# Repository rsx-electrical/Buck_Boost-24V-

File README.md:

# Buck_Boost
Designed to provide a regulated 24V output from a 6S (24V nominal) battery pack with an input range of about 19–25V.
Intended for use in a rover system powering comms hardware (TpLink POE; JETSON AGX ORIN).

# Workflow
1. Message Discord that you are working in the repo. Nobody else can work on it once you message.
2. `git clone git@github.com:rsx-electrical/Buck_Boost-24V-.git`
3. Edit 4_switch_Buck_Boost
4. Edit the README in 4_switch_Buck_Boost to describe what your commit does and why the changes were made.
5. Save a zip file version of your finished work into History Folder. 
- File should named `<date/time>_<name>_<brief_description_of_changes>`
5. Stage the files you want to commit. See "How to commit changes" bellow. 
6. `git commit -m <commit message>`
7. `git push`
8. Yay:). You are done

# Specs 
Vin: 19–25V (6S Li-ion pack)
Vout: 24V nominal
Estimated power: 100W total (More than sum of both loads, some margin for overhead and future changes)

# Notes
Design is still in development; input range, component choices, and power ratings may change. Focus is on stable 24V output, good efficiency, and reliable operation in a mobile rover environment.Future updates will include board revisions, layout improvements, and performance testing.

# How to commit changes
A file with changes can be in one of three states: untracked, modified, or staged. Only staged files are included in the next commit. 
- `git status`: command to see the status of the files you have modified
## Staged files
Staged changes are changes in files that have been marked in git to be included in the next commit. The section labeled "Changes to be committed" in git status shows these staged files.
If you stage a file and then make additional changes to it, those new changes are not staged and will not be included in the next commit. To include them, you need to stage the file again.
- `git add <file_name> `: command to stage a file
- `git add . `: stage all files with changes in them. Be careful as this will also stage untracked files which often we do not want to be staged. 
- `git restore --staged <file>` : command to unstage a file
## Tracked Files
Tracked files are files that git is already monitoring for changes, meaning they were previously committed and git keeps track of any modifications to them. 
## Untracked files
Untracked files are files in your working directory that Git does not yet know about. These are sometimes autogenerated files or files for certain settings in your local repo. An example on a Mac is .DS_Store. This .DS_Store file s a hidden file created by macOS in folders to store custom metadata about that folder, like icon positions, view settings, and window size. This is not a file that we want pushed to the remote repository.

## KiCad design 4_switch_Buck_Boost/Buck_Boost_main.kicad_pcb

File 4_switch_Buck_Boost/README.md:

# Purpose of readme

This README describes each commit made to the `4_switch_Buck_Boost folder`. Add the most recent changes at the top, but below this "Purpose of readme" section.
Each commit section title in this README should follow this format: `Date, Name, Title of Commit`

## 11-07 William -- GND plane extension, board outline, connectivity fixes

Layout:

- Extended the F.Cu GND plane through the centre (including under L1) and filled the top centre with GND.
- GNDA is now an island on In1, tied to GND through NT1 netlist at the U102 exposed pad.
- Rerouted LSP/LSN as a matched pair, added the Vout pour, fixed tight clearances (FB, Vin near Q102 gate).
- Moved TP6 to R104. Made F1/F2, TP1/TP11 and the BAT/OUTPUT pours symmetrical.
- 45° corner cuts on all pours. Board outline added: 110 x 90 mm,

Fixed opens that were already in the layout:

- SW1/SW2: U102 pins 3/26 and C8/C9 were not connected to the switch nodes. Now routed via TP3/TP4.
- In2 Vin plane was not connected to the rest of Vin. Added around 30 stitching vias (14 around the Q104 drain for heat).
- ENABLE (J3/TP10 to C114), R1 to D1, C7 GND via, U101 GND pins, FB gaps.
- R7 Kelvin footprint: added net-tie pad groups (1,2)(3,4) so DRC does not flag shorts.

Fab: 2 oz outer (for higher current) and 1 oz inner copper

## 10-18 William -- Reconfigured Analog traces and GNDA island

Configured all the analog traces and GNDA island for the new LT8390 footprint

## 10-02 William -- SW1, GND, Vout, pores

Draw and filled all the pores above along with the vias.

## 09-22 Maria -- Rsense footprint

Added Littelfuse L4CL2512 footprint for the sensing resistors. Reangered power path to accommodate size change in new resistor and inductor footprints.

## 09-20, William -- 4 Layers GND and GNDA plane

Made all the 4 Layers, Top-GND&GNDA-Vin-GND. Connected both GND and GNDA together thorugh a via and shorted resistor to prevent DRC error. Has connected all the vias in analog stage.

## 09-19, William -- Update footprint, Analog traces

Updated FETs symbols footprints, Inductor footprints, Connect traces for analog stage

## 09-12, Maria -- Reverse Polarity Protection

Added reverse polarity protection to the schematic and layout. Placed between the fuse and vin.

## 07-17, Anthony -- Template Starting Changes

Went ahead and hunkered down on some more final changes to the analog component placement, providing a tighter, more optimized orientation for building traces, closer/more compact. Def mess around with them if need be, esp the gate driver series resistors, those can go wherever you want, just pls keep the BOOTstrap caps as close as possible. With placement of analog passive components, gonna like draw gate signal traces as copper pours, up to discretion of later design review. Additionally, settled on shunt footprint/placement without compromising hot loop layout (best we gonna do, had to sacrifice snub filter, but this is optional, pick them up later). And, upgraded inductor footprint to be more 'on-brand' with the power inductors you're likely gonna find for the necessary L (uH) values that 55V/0.55A, 12V/5A are gonna demand. Please feel more than free to change any footprints you see fit. Also, omitted the fan control aux circuit, this is gonna be external to the buck-boost pcb. TLDR: slightly prepared everything to turn this 24V buck-boost into a template PCB for bucking/boosting and buck-boosting for 5V,12V,24V, and 55V.

## 07-03, Maria -- Passive Components, Controller and Auxiliary Circuits

Feedback from the June 3rd commit was that the passive component circuits should be closer to the controller. There is no need to have them so spread out and close to the power path as it should be good to have a trace to the power path. This update moves the feedback circuit, enable circuit and passive components for the controller to be closer to the controller. This update adds traces for these circuits (traces for within these Passive Components and Auxiliary Circuits only) as well as two pores for GNDA and GND (GND pore is the GND for the enable circuit). Please note that I know that the edges of these pores are rough. Turns out I am kinda sucky at drawing out pores. Also not there is no vias added. I am going to assume that these will be added once we agree with the component placement.

## 06-03, Maria -- Passive Components, Controller and Auxiliary Circuits

Added the passive components, controller and auxiliary Circuits to the power path

## 05-23, Maria -- First Attempt at power path

Uhm so this is written on June 3rd because I forgot. Soooooo yeah basically the title, first attempt at full power path.

## 04-03, William -- PCB components placement

Tried to minimize the Hot loops, further optimization may be required

## 03-17, Anthony -- Additional revisions on Schematic for Smooth Layout design for yall

Want to make layout go as smoothly as possible, so just went ahead and ensured all components had appropiate footprints. Also added NTC (temp control) for fan control using heat probe.

## List of stuff

-Added filter caps to Vin and Vout pin connections to LT8390

-Adjusted for larger Cout over Cin to reflect calculated sizing demands.

-Changed Inductor footprint for better saturation current rating/Irms rating, previous one was way to close to our shit, plus this footprint is way more streamlined imo

-Opt to use different footprint for shunt, kicad-preloads are fucking stinky uh uh (DOWNLOAD AND IMPORT SYMBOL AND FOOTPRINT PLEASE: https://www.snapeda.com/parts/KRL3216T4-M-R003-F-T1/Susumu/view-part/ )

-EN/UVLO needs voltage divider network for proper ENABLE, so adjusted level shifter circuit for ~1.2V to be seen at pin EN/UVLO, but still programs for undervoltage lockout when reach ~16V or so, good shutoff conditions in case BMS fucks us somehow -- It's a mandatory feature not preprogrammed like a lot of the TI chips are.

-Better probing points for observing ripple, PWM, or general signals (3 kinds of probe footprints). M3 Mounting holes added as well and dedicated Net tie for GNDA and GND (fuck with footprint if need be)

-Heatsink gonna be adhesive, fuck mounts, also made it an option to use osc freq or triangle spreading +/- 15%. Triangle spread usually better, but can introduce greater voltage ripple so we can place with it using jumper cap and 2x2 head conn setup.

-NTC for temp control fan will prob be wire that sits and probes heatsink, so just a CONN for now, we'll see, up to ya'll.

-All connections on schematic should roughly agree with where they'll go on layout (ie. BST caps near chip and not power stage)

-SMD trimmers, not bulky n shit (THT or SMD, if going near chip, SMD, if away from chip, THT/SMD).

-Snub filter 0805 caps, larger caps capable of handling transient response from fets way better than 402 or 603 so yeye, also shorter fuse holders too.

## 03-14, Anthony -- Final Check on shit

All pin connections/sizing good -- ready for layout

## 03-14, Maria Finish up pins and make it look pretty

I tried to make it look prettier. I may have failed at that but I finished up the pins;).

## 03-07, William, FeedBack loop trimmer and decoupling capacitor addition

Add a trimmer to ensure precise FB voltage of 1V, and a safety margin during tuning. Add Decoupling capacitor for stabilizing voltage.

## 03-06, Maria, LT8390 Pins

To be quite honest the most important part of this commit is probably this readme where I am documenting all of the questions I have about these pins. This commit is mostly my best guess. I hope to get clarification this Saturday ;).

### RT pin

This pin should have a resistor of 75kOhms attached to it. Question is should we have a potentiometer to ensure that we can tune to 75kOhms as all resistors will have some range of error on the resistance value.

### SS pin

All of the example applications have a value of 0.1u F. I don't understand how we determine the minimum soft-start time that we want. We don't add a resistance here because we want to hiccup safety mode, not latch off or keep running mode.

### Vc pin

I am so lost, I don't know my up from down for this pin.

### PGOOD pin

This pin is smth we could connect to an external microcontroller as indicator that the voltage has successfully reached its target. I don't think that this will probably be used. However connect to INTVcc with 100k ohms so that pin is pulled low when the FB pin is within �10 percent of the final regulation voltage. Maybe down the line we will want to connect it to smth, we could leave it hanging if we wanted. A value of 100kohms is used because that is used in all of the example application circuits.

### INTVcc pin

Tie to 4.7uF ceramic capacitor as instructed.

### SYNC/SPREAD

We don't want an external source for the switching. I think we probably want to have the mode with the 15 percent spread around internal oscillator frequency to ensure no sudden noise peaks. Tie this pin to INTVcc.

## 03-05, Maria, Capacitors !!!

Thank you Anthony for the document about filtering ringing and ripple!!! The document helped with this section a lot. Also thank you to the LT890 data sheet for going through a bit about Cin and Cout capacitances.

### Ringing Frequency

Ringing frequency of 75MHz-143MHz. 22nF will filter 30MHZ-100MHz range and 4.7nF will filter 100+MHz range. In a 4-switch buck-boost, the "Active Switching Side" moves depending on the mode (Buck or Boost). Therefore a 22 nF + 4.7 nF stack on required on both the Input and Output power rails to stay protected. At the high frequencies that ringing occurs at, the 15uH inductor between the two switching nodes is 2*pi*freq\*(15e-6). For a frequency of 100MHz this comes to an impedance of 9.5KOhms. Maybe we can consider using snub circuits on the switching nodes? May not be required as power rails are protected.

### Bulk Capacitors

Calculations for the following are seen on this spreadsheet under the Capacitance Values tab: https://docs.google.com/spreadsheets/d/1GE4mJHaV0VTMqPT8AXjkSjW_NcW0vJ0DrAooZ-j17pU/edit?gid=2053012627#gid=2053012627

#### Cout

We want the output ripple to be at most 2 percent of the output voltage which is 0.480V. The output capacitance required to have this output ripple under boost conditions is at least 5.21uF and under buck conditions at least a 0.781uF output capacitance is required. To account for the Boost Right-Half-Plane Zero phenomenon a minimum of 57.9uF output capacitance is required. To account for voltage undershoot an output capacitance of 1.46uF is required. Therefore for the circuit to be functional an output capacitance of at least 57.9uF is required. We want low ESR. Two capacitances of 33uF can be used.

#### Cin

A Cin of at least 1.14uF is required to maintain under a input voltage ripple of 0.512V. However the input capacitance network should support a Irms current of Iout(max)/2 (see pg. 21 of LT8390 data sheet). No capacitor that small can support that large of a current. We also want a very small ESR. Therefore we should have larger capacitance values in parallel to split the current and lower ESR. For electrolytic capacitors that have smaller values their ESR is very large. Is it better to have only ceramic at the beginning. For now, I am going to put a placeholder value of three 22nF electrolytic capacitors or Cin. This will lower ESR and provide required capacitance. Ask this Saturday which type of capacitor would be best here. I feel like it would be ceramic.
####Next Steps
Next steps would be determining the exact capacitors required. Most of this is gonna be a fight of finding capacitors with low ESRs. If all falls apart can just use capacitors with higher values and have more in parallel to lower ESR (generally larger value electrolytic capacitors have lower ESRs). I am uncertain if we are just gonna use capacitors we have in stock. Smth I will have to ask Anthony.

## 02-27, Maria, High Side Switch

2N7002K: rsx nmos
BSS83P: rsx pmos only has Vds of 30V. rsx pmos is cutting it close because our vin can be 25ish. Dangerous if there are any spikes in our Vin. Chosen because it has a Vds of -60V which is very safe.
R106&R105: The Vgs of the pmos (BSS83P) is +/- 20V. Having this voltage divide means that the gate of the pmos will be half the voltage of Vin. This will allow the pmos to turn on when required but have a Vgs range of 9V to 13V when the enable pin is on and it will be around 0 when the enable pin if off. These are aat least 1.46ll safe ranges.

### Next Steps

Find the spec for the LEDs that rsx has in stock. Find out what the input voltage we will get from the microcontroller. Use this information to determine the exact values for the resistors at the gate of the nmos.

### LTSpice Simulation

#### High Side Switch Vin is 25.6V

PMOS high-side switch LTSpice schematic with Vin of 25.6V

When the enable input coming from a microcontroller (enable_vin) is set high, the enable pin (en_pin) on the LT8390 is set high. When the enable input is set low, the enable pin on the LT8390 is set low as well.

The Vgs (Vpmos_gate - Vin) and Vds (Ven_pin - Vin) of the pmos. Vgs is safe within the maximum of +/- 20V. Vds is safe with a maximum of -60V.

The Vgs (Ven_pin) and Vds (Vnmos_drain) of the nmos. Vgs is safe within the maximum of +/- 20V. Vds is safe with a maximum of 60V.

pmos Id is rated for -0.33A, nmos is rated for 320mA. Currents are in a safe range.

#### High Side Switch Vin is 18V

PMOS high-side switch LTSpice schematic with Vin of 18V.

When the enable input coming from a microcontroller (enable_vin) is set high, the enable pin (en_pin) on the LT8390 is set high. When the enable input is set low, the enable pin on the LT8390 is set low as well.

The Vgs (Vpmos_gate - Vin), Vds (Ven_pin - Vin) and Id of the pmos. Vgs is safe within the maximum of +/- 20V. Vds is safe with a maximum of -60V. Id is safe as pmos is rated for -0.33A.

The Vgs (Ven_pin) and Vds (Vnmos_drain) of the nmos. Vgs is safe within the maximum of +/- 20V. Vds is safe with a maximum of 60V.

nmos current is good.

## 02-07, Maria, Reformat to be readable

Reformat to be split up into sections like the example Anthony gave us of a past boost converter. Input filtering capacitors with no values. They are placeholders. Values will need to be determined and number of capacitors will need to be determined.

## 02-05, Maria, connected power path to chip

Yeah I know title doesn't make sense. Added power path (MOSFETTS and inductor) to schematic. Connected FB. Vout/Vfb = 24. Chosen resistance values are (232 + 10)/10 =24.2. The ratio is correct; however, I assume these values may be changes for resistors rsx has in storage. 603 resistors are used because low power will flow through them. Shunt resistors are used for current sensing. Again these may be replaces with resistance values for resistors we already have. The math for these values can be found in the Google doc. Capacitors for the BST1 and BST2 are 2.5uC because gate charge of MOSFETTs are 2.5e-8C and the capacitance should be 100x the gate charge. Things needed to be talked about: do we want to use shunt resistors, and what resistors do we have in stock to choose from.

## 01-17, Anthony, added selection of res and caps

Basically just put in a couple of diff types of res and caps and their respective footprints (ceramic, polarized, shunt, basic shit that we'll prob use in the future, just pay attention to what each footprint corresponding to each symbol belongs to).

603 and 805 usually for IC filtering with 805 for larger analog symbols (LDOs) and 1206 usually for bulk cap filtering of noise at input/outputs. Polarized caps used for stabilizing voltage/reducing ripple/storing energy/etc.

603 and res up usually depend on power dissipation, with the shunt being the widest and likely used for current sensing, if choose to go down this route into design, may need to change footprint, the Vishay one is overpowered and like for 0.0001ohm applications, which is, nah.

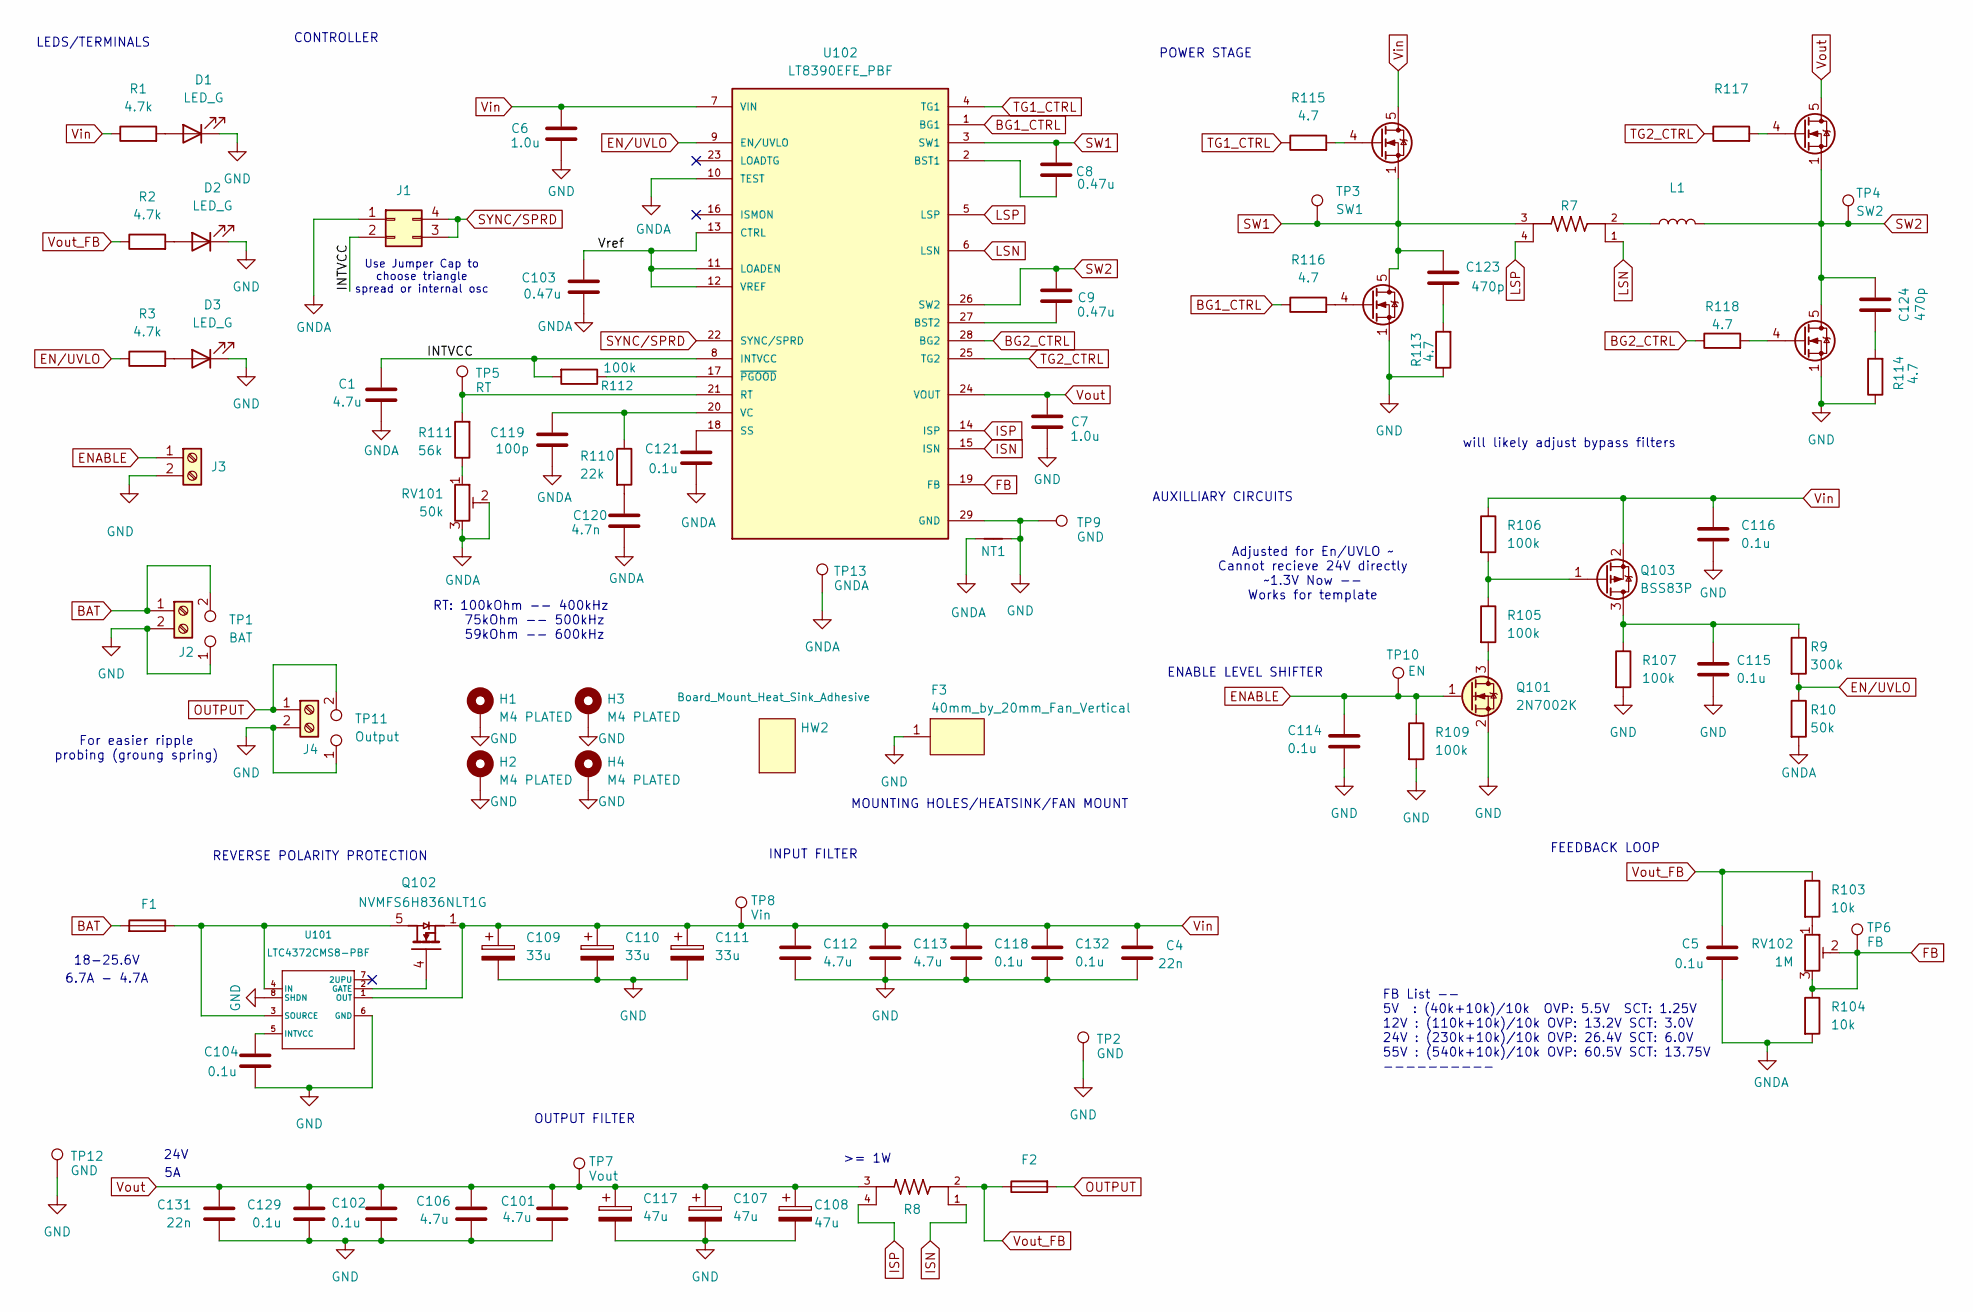
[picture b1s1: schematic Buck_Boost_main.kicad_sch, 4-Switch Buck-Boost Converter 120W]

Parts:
C1, C101, C106, C112, C113: 4.7u; C_0805_2012Metric
C4, C131: 22n; C_0603_1608Metric
C5, C102, C104, C114, C115, C116, C118, C121, C129, C132: 0.1u; C_0603_1608Metric
C6, C7: 1.0u; C_0603_1608Metric
C8, C9, C103: 0.47u; C_0603_1608Metric
C107, C108, C117: 47u; CP_Elec_8x10.5
C109, C110, C111: 33u; CP_Elec_8x10.5
C119: 100p; C_0603_1608Metric
C120: 4.7n; C_0603_1608Metric
C123, C124: 470p; C_0805_2012Metric
D1, D2, D3: LED_G; LED_0805_2012Metric; MPN LTST-C170GKT
F1, F2: Fuse_Holder_Auto; Fuseholder_Blade_Mini_Keystone_3568; MPN 3568-10
F3: 40mm_by_20mm_Fan_Vertical; 40mmFan; MPN THA0412AD
H1, H2, H3, H4: M4 PLATED; MountingHole_3.2mm_M3_Pad_Via
HW2: Board_Mount_Heat_Sink_Adhesive; BDN10-3CB_A01; MPN BDN10-3CB/A01
J1: Conn_02x02_Counter_Clockwise; PinHeader_2x02_P2.54mm_Vertical
J2, J4: Screw_Terminal_2x5.08; Molex_0398800302; MPN 398800302
J3: Screw_Terminal_2x2.54; Wurth_691210910002; MPN 691210910002
L1: L_Bourns_SRP1770TA_16.9x16.9mm; MPN PQ2617BHA-150K
NT1: NetTie_2; NetTie-2_SMD_Pad0.5mm
Q101: 2N7002K; SOT-23; MPN 2N7002K-T1-E3
Q102: NVMFS6H836NLT1G; ONSemi_SO-8FL_488AA
Q103: BSS83P; SOT-23
Q104, Q105, Q106, Q107: BSC070N10LS5; TDSON-8-1
R1, R2, R3: 4.7k; R_0603_1608Metric
R7: WLTM0612_R002-R100_Kelvin; PARTREV N/A
R8: Littelfuse_L4CA0612_4Terminal; PARTREV N/A
R9: 300k; R_0603_1608Metric
R10: 50k; R_0603_1608Metric
R103, R104: 10k; R_0603_1608Metric
R105, R106, R107, R109, R112: 100k; R_0603_1608Metric
R110: 22k; R_0603_1608Metric
R111: 56k; R_0603_1608Metric
R113, R114, R115, R116, R117, R118: 4.7; R_0603_1608Metric
RV101: 50k; Potentiometer_Bourns_3314G_Vertical
RV102: 1M; Potentiometer_Bourns_3314G_Vertical
TP1: BAT; TestPoint_2Pads_Pitch2.54mm_Drill0.8mm
TP2, TP9, TP12: GND; TestPoint_Pad_D1.0mm
TP3: SW1; TestPoint_Loop_D2.50mm_Drill1.0mm_LowProfile
TP4: SW2; TestPoint_Loop_D2.50mm_Drill1.0mm_LowProfile
TP5: RT; TestPoint_Pad_D1.0mm
TP6: FB; TestPoint_Pad_D1.0mm
TP7: Vout; TestPoint_Pad_D1.0mm
TP8: Vin; TestPoint_Pad_D1.0mm
TP10: EN; TestPoint_Pad_D1.0mm
TP11: Output; TestPoint_2Pads_Pitch2.54mm_Drill0.8mm
TP13: GNDA; TestPoint_Pad_D1.0mm
U101: LTC4372CMS8-PBF; MS8_05-08-1660_ADI
U102: LT8390EFE_PBF; 05-08-1663_ADI; PARTREV B

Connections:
/INTVCC: C1.2, J1.2, R112.2, U102.8 (INTVCC)
/Vref: C103.2, U102.11 (LOADEN), U102.12 (VREF), U102.13 (CTRL)
BAT: F1.1, J2.1, TP1.2
BG1_CTRL: R116.1, U102.1 (BG1)
BG2_CTRL: R118.1, U102.28 (BG2)
ENABLE: C114.1, J3.1, Q101.1 (G), R109.1, TP10.1
EN/UVLO: R3.1, R9.2, R10.1, U102.9 (EN/UVLO)
FB: R104.1, RV102.2, RV102.3, TP6.1, U102.19 (FB)
GND: C4.2, C6.1, C7.1, C101.2, C102.2, C104.2, C106.2, C107.2, C108.2, C109.2, C110.2, C111.2, C112.2, C113.2, C114.2, C115.2, C116.2, C117.2, C118.2, C129.2, C131.2, C132.2, D1.1 (K), D2.1 (K), D3.1 (K), F3.1, H1.1, H2.1, H3.1, H4.1, J2.2, J3.2, J4.2, NT1.2, Q101.2 (S), Q106.1 (S), Q106.2, Q106.3, Q107.1 (S), Q107.2, Q107.3, R107.2, R109.2, R113.1, R114.1, TP1.1, TP2.1, TP9.1, TP11.1, TP12.1, U101.6 (GND), U101.8 (SHDN), U102.29 (GND)
GNDA: C1.1, C5.2, C103.1, C119.2, C120.2, C121.2, J1.1, NT1.1, R10.2, R104.2, RV101.2, RV101.3, TP13.1, U102.10 (TEST)
ISN: R8.1, U102.15 (ISN)
ISP: R8.4, U102.14 (ISP)
LSN: R7.1, U102.6 (LSN)
LSP: R7.4, U102.5 (LSP)
unnamed: C120.1, R110.2
unnamed: C123.2, R113.2
unnamed: C124.1, R114.2
unnamed: D1.2 (A), R1.2
unnamed: D2.2 (A), R2.2
unnamed: D3.2 (A), R3.2
unnamed: L1.1, R7.2
unnamed: Q101.3 (D), R105.2
unnamed: F1.2, Q102.5 (D), U101.3 (SOURCE), U101.4 (IN)
unnamed: Q102.4 (G), U101.2 (GATE)
unnamed: C115.1, Q103.3 (D), R9.1, R107.1
unnamed: Q103.1 (G), R105.1, R106.2
unnamed: Q104.4 (G), R115.2
unnamed: Q105.4 (G), R117.2
unnamed: Q106.4 (G), R118.2
unnamed: Q107.4 (G), R116.2
unnamed: R103.2, RV102.1
unnamed: R111.1, RV101.1
unnamed: C104.1, U101.5 (INTVCC)
unnamed: C8.1, U102.2 (BST1)
unnamed: C9.1, U102.27 (BST2)
unnamed: R111.2, TP5.1, U102.21 (RT)
unnamed: C121.1, U102.18 (SS)
unnamed: C119.1, R110.1, U102.20 (VC)
unnamed: R112.1, U102.17 (~PGOOD)
OUTPUT: F2.1, J4.1, TP11.2
SW1: C8.2, C123.1, Q104.1 (S), Q104.2, Q104.3, Q107.5 (D), Q107.6, Q107.7, Q107.8, R7.3, TP3.1, U102.3 (SW1)
SW2: C9.2, C124.2, L1.2, Q105.1 (S), Q105.2, Q105.3, Q106.5 (D), Q106.6, Q106.7, Q106.8, TP4.1, U102.26 (SW2)
SYNC/SPRD: J1.3, J1.4, U102.22 (SYNC/SPRD)
TG1_CTRL: R115.1, U102.4 (TG1)
TG2_CTRL: R117.1, U102.25 (TG2)
Vin: C4.1, C6.2, C109.1, C110.1, C111.1, C112.1, C113.1, C116.1, C118.1, C132.1, Q102.1 (S), Q102.2 (S), Q102.3 (S), Q103.2 (S), Q104.5 (D), Q104.6, Q104.7, Q104.8, R1.1, R106.1, TP8.1, U101.1 (OUT), U102.7 (VIN)
Vout: C7.2, C101.1, C102.1, C106.1, C107.1, C108.1, C117.1, C129.1, C131.1, Q105.5 (D), Q105.6, Q105.7, Q105.8, R8.3, TP7.1, U102.24 (VOUT)
Vout_FB: C5.1, F2.2, R2.1, R8.2, R103.1

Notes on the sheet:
LEDS/TERMINALS
Adjusted for En/UVLO ~ Cannot recieve 24V directly ~1.3V Now -- Works for template
INPUT FILTER
24V
REVERSE POLARITY PROTECTION
FB List -- 5V : (40k+10k)/10k OVP: 5.5V SCT: 1.25V 12V : (110k+10k)/10k OVP: 13.2V SCT: 3.0V 24V : (230k+10k)/10k OVP: 26.4V SCT: 6.0V 55V : (540k+10k)/10k OVP: 60.5V SCT: 13.75V ----------
18-25.6V
AUXILLIARY CIRCUITS
Use Jumper Cap to choose triangle spread or internal osc
RT: 100kOhm -- 400kHz 75kOhm -- 500kHz 59kOhm -- 600kHz
POWER STAGE
For easier ripple probing (groung spring)
FEEDBACK LOOP
OUTPUT FILTER
ENABLE LEVEL SHIFTER
will likely adjust bypass filters
CONTROLLER
6.7A - 4.7A
>= 1W
MOUNTING HOLES/HEATSINK/FAN MOUNT

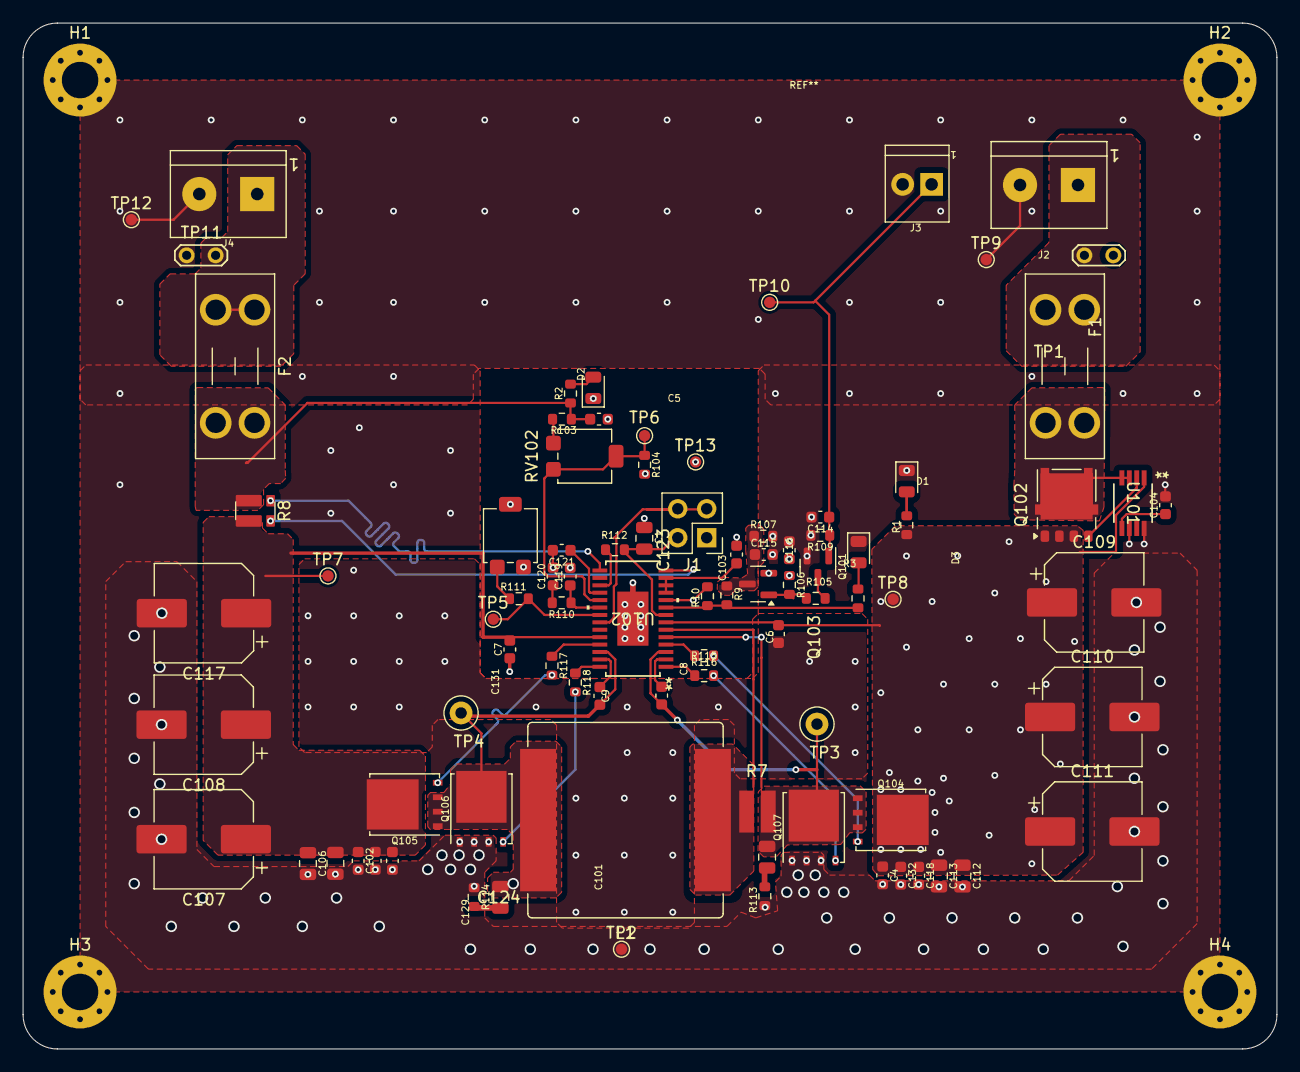
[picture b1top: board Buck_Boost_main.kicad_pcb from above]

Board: 4 copper layers, 110.0 x 90.0 mm, 95 parts (0 on the bottom side), 48 nets.

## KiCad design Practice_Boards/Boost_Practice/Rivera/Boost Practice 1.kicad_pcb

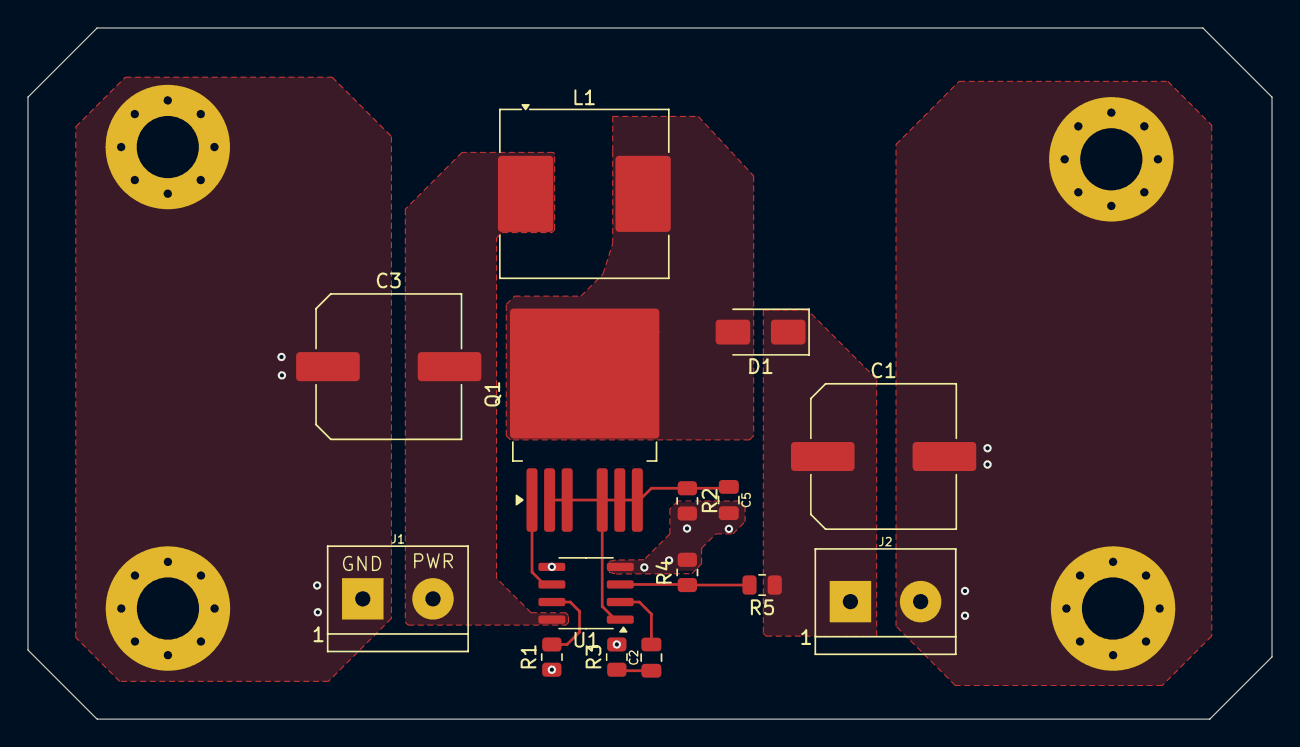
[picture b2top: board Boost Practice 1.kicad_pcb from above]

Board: 2 copper layers, 90.0 x 50.0 mm, 19 parts (0 on the bottom side), 10 nets.

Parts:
C1, C3: 100uF; C_Elec_10x10.2
C2: 22nF; C_0805_2012Metric
C5: 0.01uF; C_0805_2012Metric
D1: D_Schottky; D_SMA
H1, H2, H3, H4: M4 PLATED; MountingHole_4.5mm_Pad_Via
J1, J2: Screw_Terminal_2x5.08; Molex_0398800302
L1: 10uH; L_Coilcraft_MSS1260H-XXX
Q1: IPB180N10S4-02; TO-263-6
R1: 40k; R_0805_2012Metric
R2: 0.025; R_0805_2012Metric
R3: 4.7k; R_0805_2012Metric
R4: 20k; R_0805_2012Metric
R5: 60k; R_0805_2012Metric
U1: LM3478MA; SOIC-8_3.9x4.9mm_P1.27mm

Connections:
/Vin: C3.2, J1.2, L1.1, U1.8 (V_{IN})
/Vout: C1.1, D1.1 (K), J2.1, R5.1
GND: C1.2, C3.1, C5.2, H1.1, H2.1, H3.1, H4.1, J1.1, J2.2, R1.1, R2.2, R3.2, R4.2, U1.4 (AGND), U1.5 (PGND)
unnamed: C2.1, R3.1
unnamed: D1.2 (A), L1.2, Q1.4 (D)
unnamed: Q1.1 (G), U1.6 (DR)
unnamed: C2.2, U1.2 (COMP)
unnamed: R1.2, U1.7 (FA/SD)
unnamed: R4.1, R5.2, U1.3 (FB)
unnamed: C5.1, Q1.2 (S), Q1.3 (S), Q1.5 (S), Q1.6 (S), Q1.7 (S), R2.1, U1.1 (I_{SEN})

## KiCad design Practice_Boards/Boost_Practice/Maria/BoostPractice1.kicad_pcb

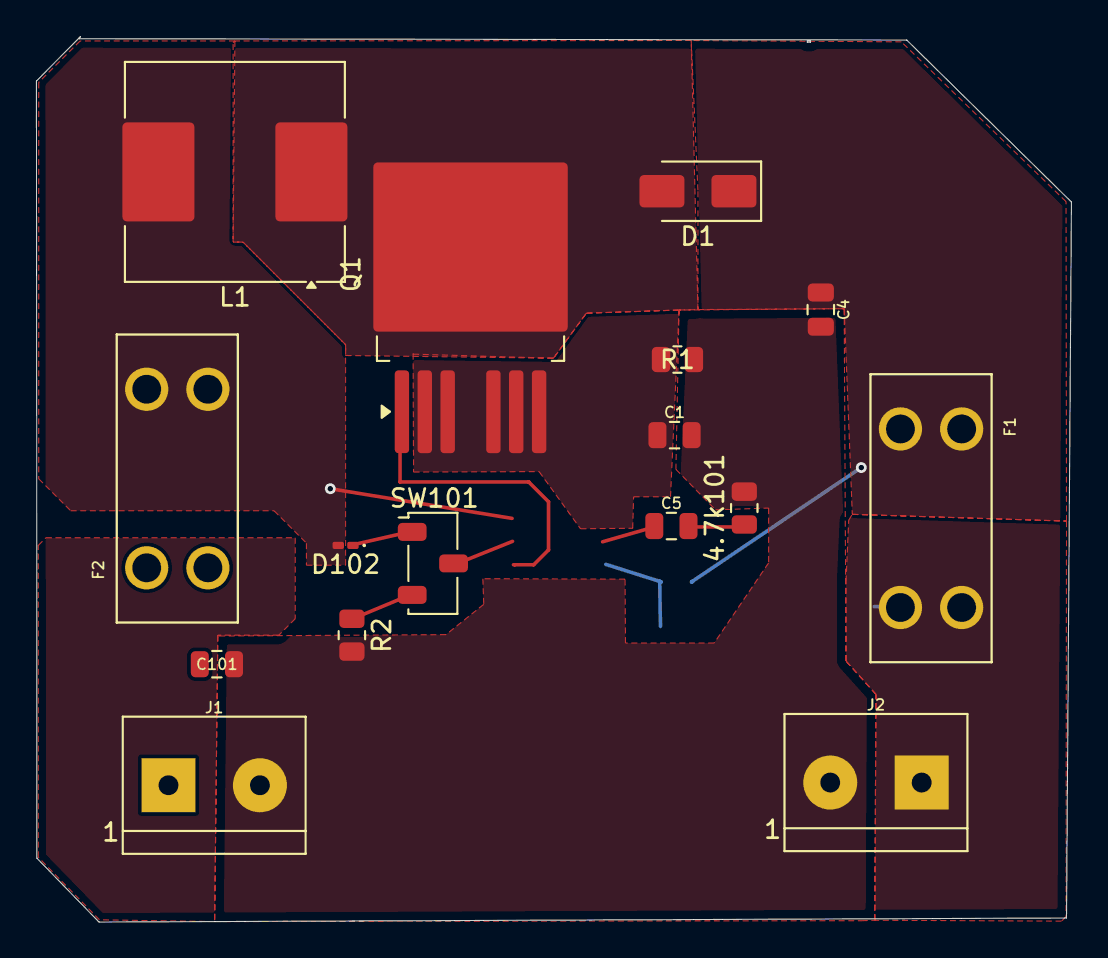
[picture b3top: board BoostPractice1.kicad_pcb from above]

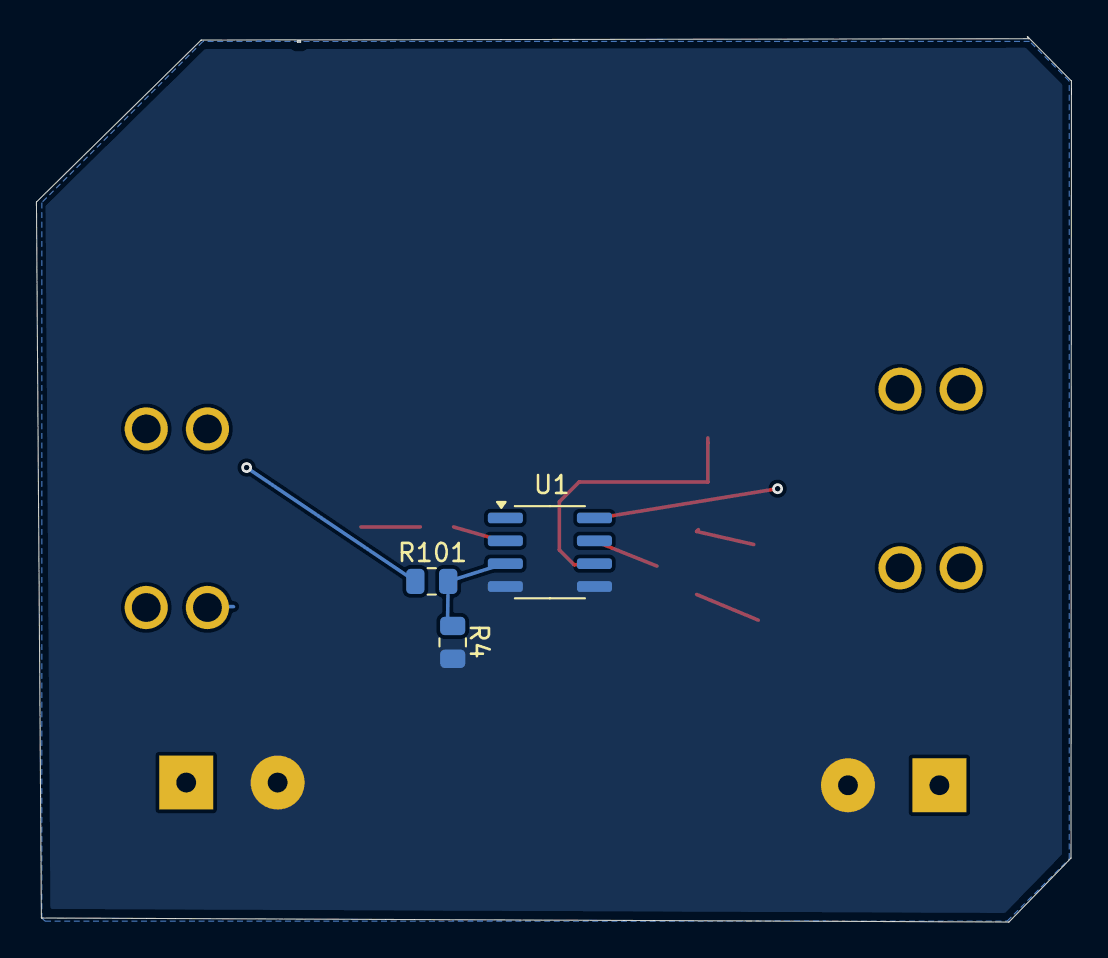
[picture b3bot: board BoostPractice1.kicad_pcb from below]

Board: 2 copper layers, 57.5 x 49.2 mm, 19 parts (3 on the bottom side), 14 nets, no tracks yet.

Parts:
4.7k101: R; R_0805_2012Metric
C1: 0.01u; C_0805_2012Metric
C4, C101: 100u; C_0805_2012Metric
C5: 22n; C_0805_2012Metric
D1: D_Schottky; D_SMA
D102: LED; LED_0201_0603Metric_Pad0.64x0.40mm_HandSolder
F1, F2: Fuse_Holder_Auto; FUSE_3568-10
J1, J2: Screw_Terminal_2x5.08; Molex_0398800302
L1: 10u; L_Coilcraft_MSS1260H-XXX
Q1: IPB180N10S4-02; TO-263-6
R1: 0.025; R_0805_2012Metric
R2: 40k; R_0805_2012Metric
R4: 20k; R_0805_2012Metric
R101: 60k; R_0805_2012Metric
SW101: SW_Nidec_CAS-120A1; Nidec_Copal_CAS-120A
U1: LM3478MA; SOIC-8_3.9x4.9mm_P1.27mm

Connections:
/COMP: C5.1, U1.2 (COMP)
/DR: Q1.1 (G), U1.6 (DR)
/Isen: C1.1, Q1.2 (S), Q1.3 (S), Q1.5 (S), Q1.6 (S), Q1.7 (S), R1.1, U1.1 (I_{SEN})
/V_FA/SD: SW101.2 (B), U1.7 (FA/SD)
/V_FB: R4.1, R101.2, U1.3 (FB)
/V_LED_ON: D102.1 (K), SW101.1 (C)
/V_boost_mode: R2.1, SW101.3 (A)
/V_ind: D1.2 (A), L1.1, Q1.4 (D)
/Vin: C101.1, F2.1, J1.1
/Vin_after_fuse: D102.2 (A), F2.2, L1.2, U1.8 (V_{IN})
/Vout: F1.2, J2.2
/Vout_before_fuse: C4.1, D1.1 (K), F1.1, R101.1
GND: 4.7k101.2, C1.2, C4.2, C101.2, J1.2, J2.1, R1.2, R2.2, R4.2, U1.4 (AGND), U1.5 (PGND)
unnamed: 4.7k101.1, C5.2

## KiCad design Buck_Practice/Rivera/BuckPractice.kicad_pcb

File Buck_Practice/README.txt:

Place your current progress in this folder, and ping me when you do. I'll be able to view it and make comments, and you can pull it from the GitHub and continue with any additional work, and push your final iteration.

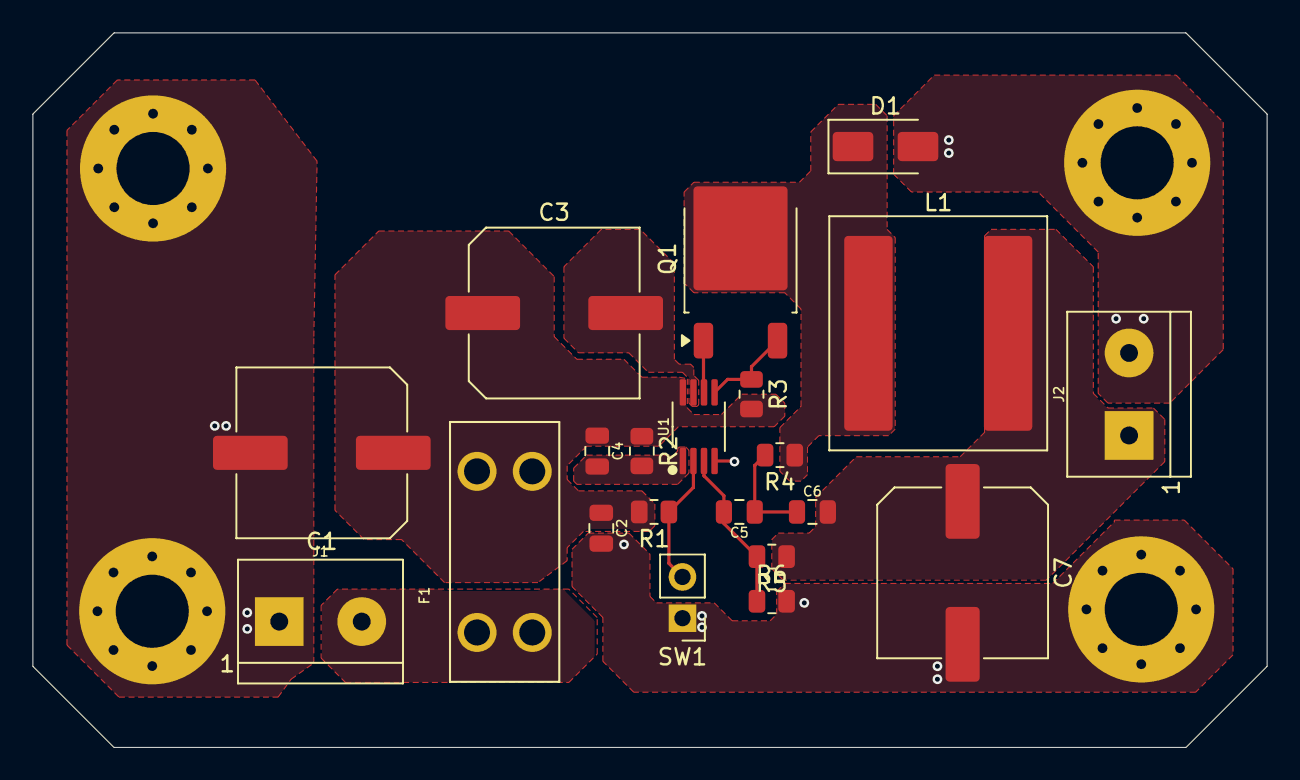
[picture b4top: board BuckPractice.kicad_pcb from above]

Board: 2 copper layers, 76.0 x 44.0 mm, 25 parts (0 on the bottom side), 12 nets.

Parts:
C1: 33 u; C_Elec_10x10.2
C2: 1u; C_0805_2012Metric
C3: 0.47u; C_Elec_10x10.2
C4: 1000p; C_0805_2012Metric
C5: 0.1u; C_0805_2012Metric
C6: 3300p; C_0805_2012Metric
C7: 100u; C_Elec_10x10.2
D1: D_Schottky; D_SMA
F1: Fuse_Holder_Auto; FUSE_3568-10
H1, H2, H3, H4: M4 PLATED; MountingHole_4.5mm_Pad_Via
J1, J2: Screw_Terminal_2x5.08; Molex_0398800302
L1: 15u; L_Coilcraft_XAL1350-XXX
Q1: QM6015D; TO-252-2
R1: 90.9k; R_0805_2012Metric
R2: 2.1k; R_0805_2012Metric
R3: 0.01; R_0805_2012Metric
R4: 66.5k; R_0805_2012Metric
R5: 10k; R_0805_2012Metric
R6: 3.4k; R_0805_2012Metric
SW1: SW_SPST; PinHeader_1x02_P2.54mm_Vertical
U1: LM25085MM; MSOP-8_3x3mm_P0.65mm_DL

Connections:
/Vin: F1.1, J1.2
/Vout: C6.2, C7.1, J2.1, L1.2, R5.1
GND: C1.2, C2.2, C7.2, D1.2 (A), H1.1, H2.1, H3.1, H4.1, J1.1, J2.2, R6.2, SW1.1 (A), U1.4 (GND)
unnamed: C5.1, C6.1, R4.2
unnamed: D1.1 (K), L1.1, Q1.2 (D), R4.1
unnamed: Q1.1 (G), U1.6 (PGATE)
unnamed: Q1.3 (S), R3.1, U1.5 (ISEN)
unnamed: R1.1, SW1.2 (B), U1.2 (RT)
unnamed: C4.2, R2.2, U1.1 (ADJ)
unnamed: C5.2, R5.2, R6.1, U1.3 (FB)
unnamed: C3.2, U1.7 (VCC)
unnamed: C1.1, C2.1, C3.1, C4.1, F1.2, R1.2, R2.1, R3.2, U1.8 (VIN)

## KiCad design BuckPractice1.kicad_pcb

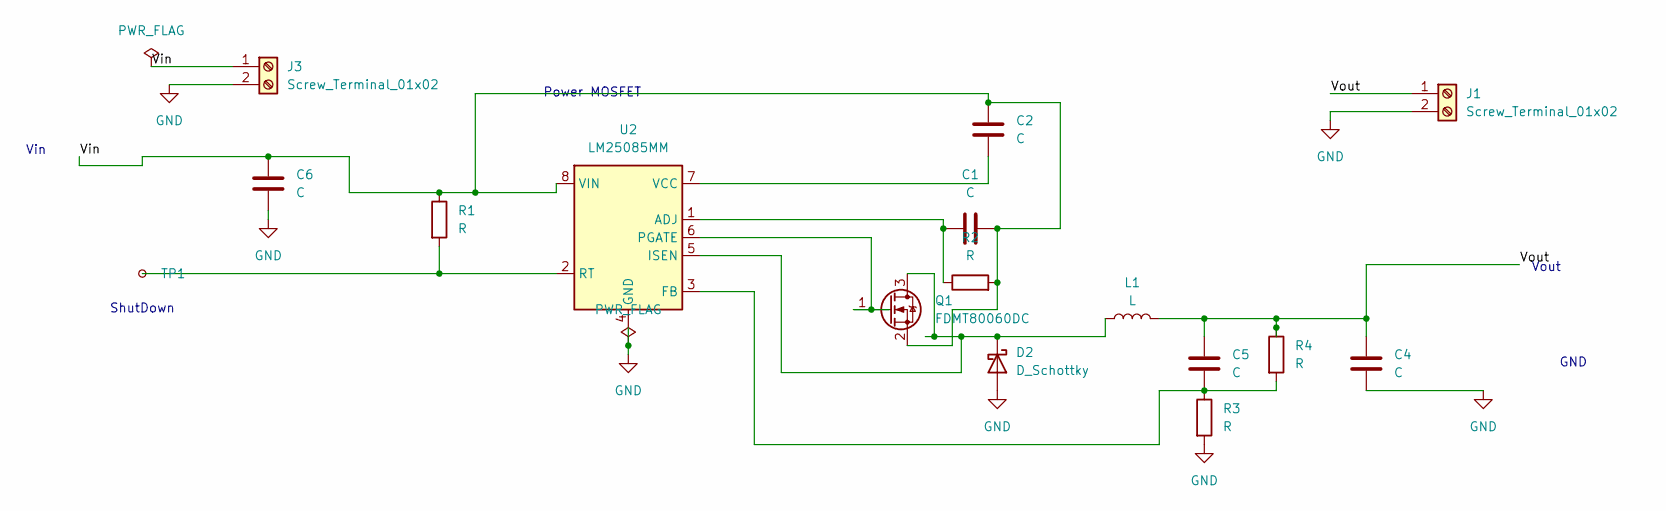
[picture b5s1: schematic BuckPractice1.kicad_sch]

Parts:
C1, C5: C; C_0805_2012Metric; MPN CL21B105KBFNNNE
C2, C4, C6: C; C_Elec_10x10.2
D2: D_Schottky; D_SMA
J1, J3: Screw_Terminal_01x02; TerminalBlock_4Ucon_1x02_P3.50mm_Vertical
L1: L; L_Coilcraft_XAL1350-XXX
Q1: FDMT80060DC; PQFN_8x8
R1, R2, R3, R4: R; R_0805_2012Metric
TP1: TestPoint_Small; TestPoint_Pad_D1.0mm
U2: LM25085MM; MSOP-8_3x3mm_P0.65mm

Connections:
/Vin: C1.2, C2.1, C6.1, J3.1, Q1.2 (S), R1.1, R2.2, U2.8 (VIN)
/Vout: C4.1, C5.2, J1.1, L1.2, R4.1
GND: C4.2, C6.2, D2.2 (A), J1.2, J3.2, R3.2, U2.4 (GND)
unnamed: D2.1 (K), L1.1, Q1.3 (D), U2.5 (ISEN)
unnamed: Q1.1 (G), U2.6 (PGATE)
unnamed: C1.1, R2.1, U2.1 (ADJ)
unnamed: C5.1, R3.1, R4.2, U2.3 (FB)
unnamed: R1.2, TP1.1, U2.2 (RT)
unnamed: C2.2, U2.7 (VCC)

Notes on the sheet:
GND
Vin
Vout
Power MOSFET
ShutDown

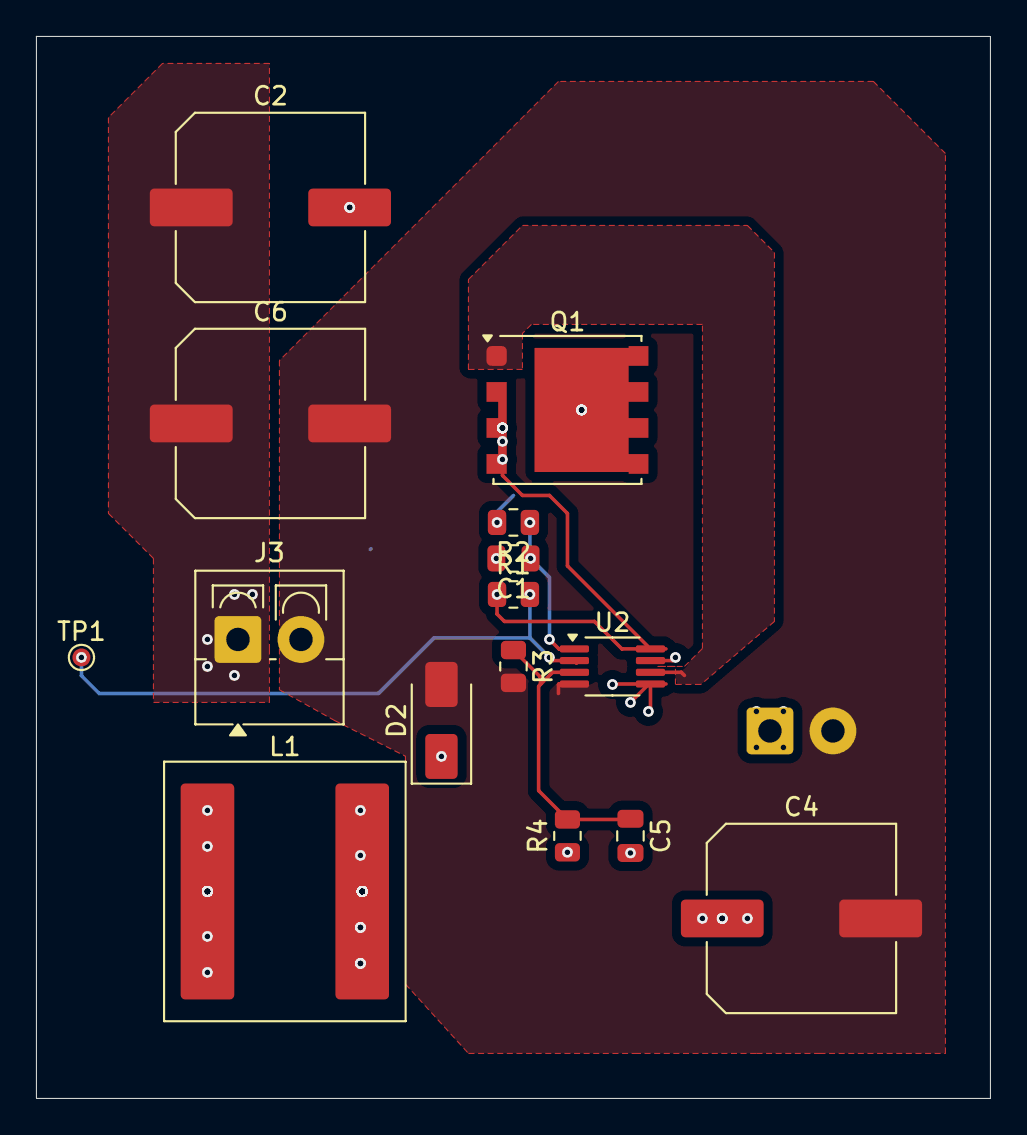
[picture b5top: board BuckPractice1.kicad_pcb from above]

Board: 2 copper layers, 53.0 x 59.0 mm, 16 parts (1 on the bottom side), 9 nets.

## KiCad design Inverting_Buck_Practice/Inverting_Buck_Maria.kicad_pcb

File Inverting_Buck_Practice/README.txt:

Happy Birthday. Place your current progress in this folder, and ping me when you do. I'll be able to view it and make comments, and you can pull it from the GitHub and continue with any additional work, and push your final iteration.

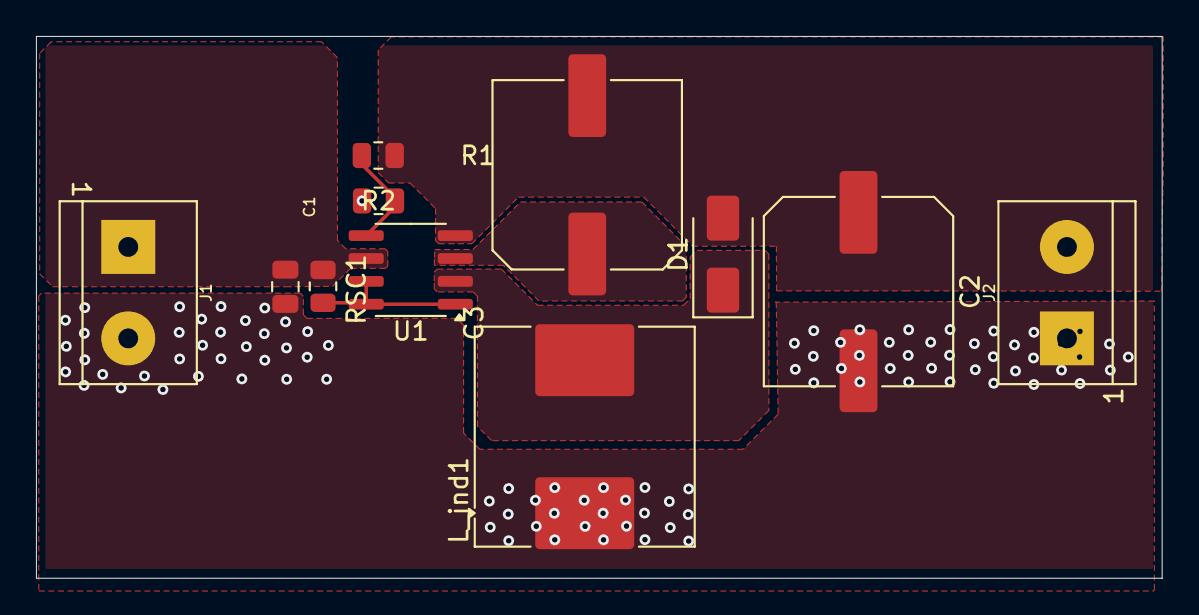
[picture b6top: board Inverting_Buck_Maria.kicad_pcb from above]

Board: 2 copper layers, 62.5 x 30.1 mm, 11 parts (0 on the bottom side), 7 nets.

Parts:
C1: 100u; C_0805_2012Metric
C2: 0.36m; C_Elec_10x10.2
C3: 1.8n; C_Elec_10x10.2
D1: D_Schottky; D_SMA
J1, J2: Screw_Terminal_2x5.08; Molex_0398800302
L_ind1: 0.18m; L_Coilcraft_MSS1260H-XXX
R1: 1500; R_0805_2012Metric
R2: 900; R_0805_2012Metric
RSC1: 0.42; R_0805_2012Metric
U1: MC33063AD; SOIC-8_3.9x4.9mm_P1.27mm

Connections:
/V_in: C1.1, J1.1, RSC1.1, U1.6 (Vin)
/V_in_after_Rsc: RSC1.2, U1.1 (SwC), U1.7 (Ipk), U1.8 (DC)
/V_ind: D1.1 (K), L_ind1.2, U1.2 (SwE)
/V_out: C2.1, C3.2, D1.2 (A), J2.2, R1.1, U1.4 (GND)
/V_volt_divider: R1.2, R2.1, U1.5 (Vfb)
GND: C1.2, C2.2, J1.2, J2.1, L_ind1.1, R2.2
unnamed: C3.1, U1.3 (TC)
